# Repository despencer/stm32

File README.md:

# stm32
Some experimental and demo stuff for STM32 programming

# Building projects
mkdir build/<prjname>

cd buid/<prjname>

cmake <prjpath> -DBOARD=<board>

make

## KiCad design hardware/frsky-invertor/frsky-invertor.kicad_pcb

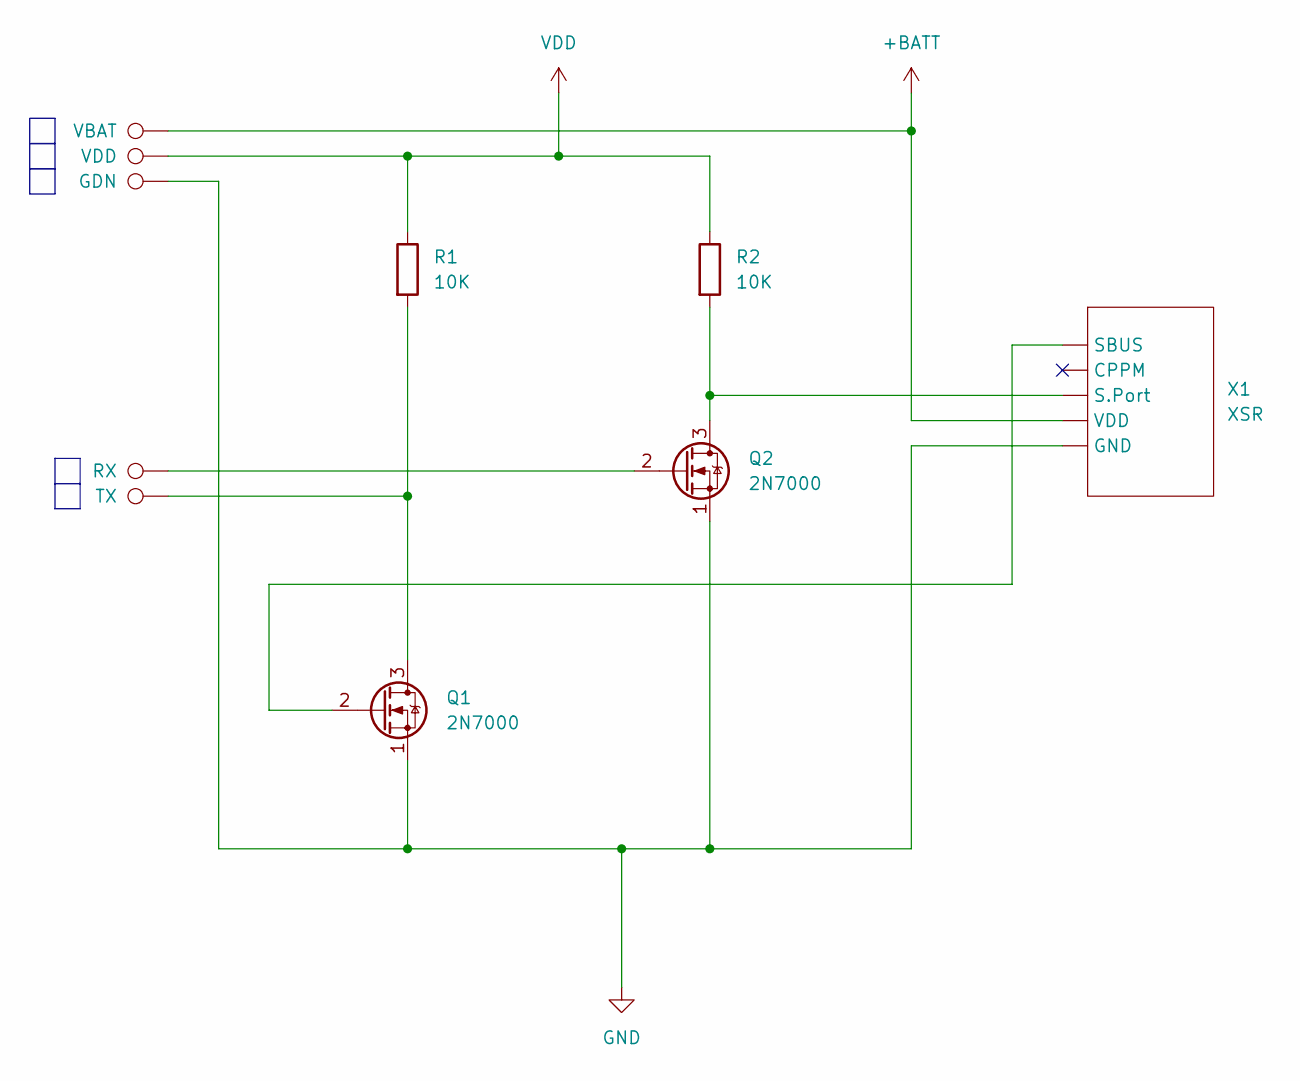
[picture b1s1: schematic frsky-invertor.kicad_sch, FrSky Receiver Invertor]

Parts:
Q1, Q2: 2N7000; TO-92_Inline_Wide
R1, R2: 10K; R_Axial_DIN0411_L9.9mm_D3.6mm_P12.70mm_Horizontal
TP1: GDN; SolderWire-0.1sqmm_1x01_D0.4mm_OD1mm
TP2: VDD; SolderWire-0.1sqmm_1x01_D0.4mm_OD1mm
TP3: VBAT; SolderWire-0.1sqmm_1x01_D0.4mm_OD1mm
TP4: TX; SolderWire-0.1sqmm_1x01_D0.4mm_OD1mm
TP5: RX; SolderWire-0.1sqmm_1x01_D0.4mm_OD1mm
X1: XSR

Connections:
+BATT: TP3.1, X1.4 (VDD)
GND: Q1.1 (S), Q2.1 (S), TP1.1, X1.5 (GND)
unnamed: Q1.3 (D), R1.2, TP4.1
unnamed: Q1.2 (G), X1.1 (SBUS)
unnamed: Q2.3 (D), R2.2, X1.3 (S.Port)
unnamed: Q2.2 (G), TP5.1
VDD: R1.1, R2.1, TP2.1

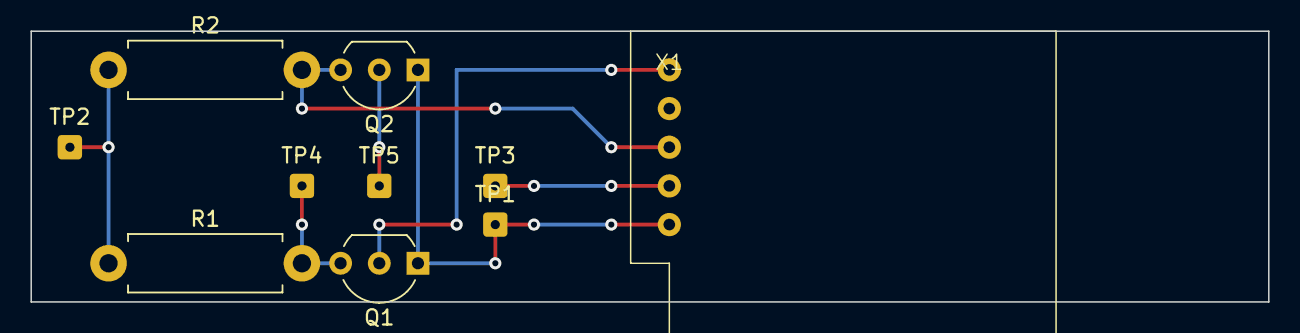
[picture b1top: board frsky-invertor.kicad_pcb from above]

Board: 2 copper layers, 81.3 x 17.8 mm, 10 parts (0 on the bottom side), 7 nets.

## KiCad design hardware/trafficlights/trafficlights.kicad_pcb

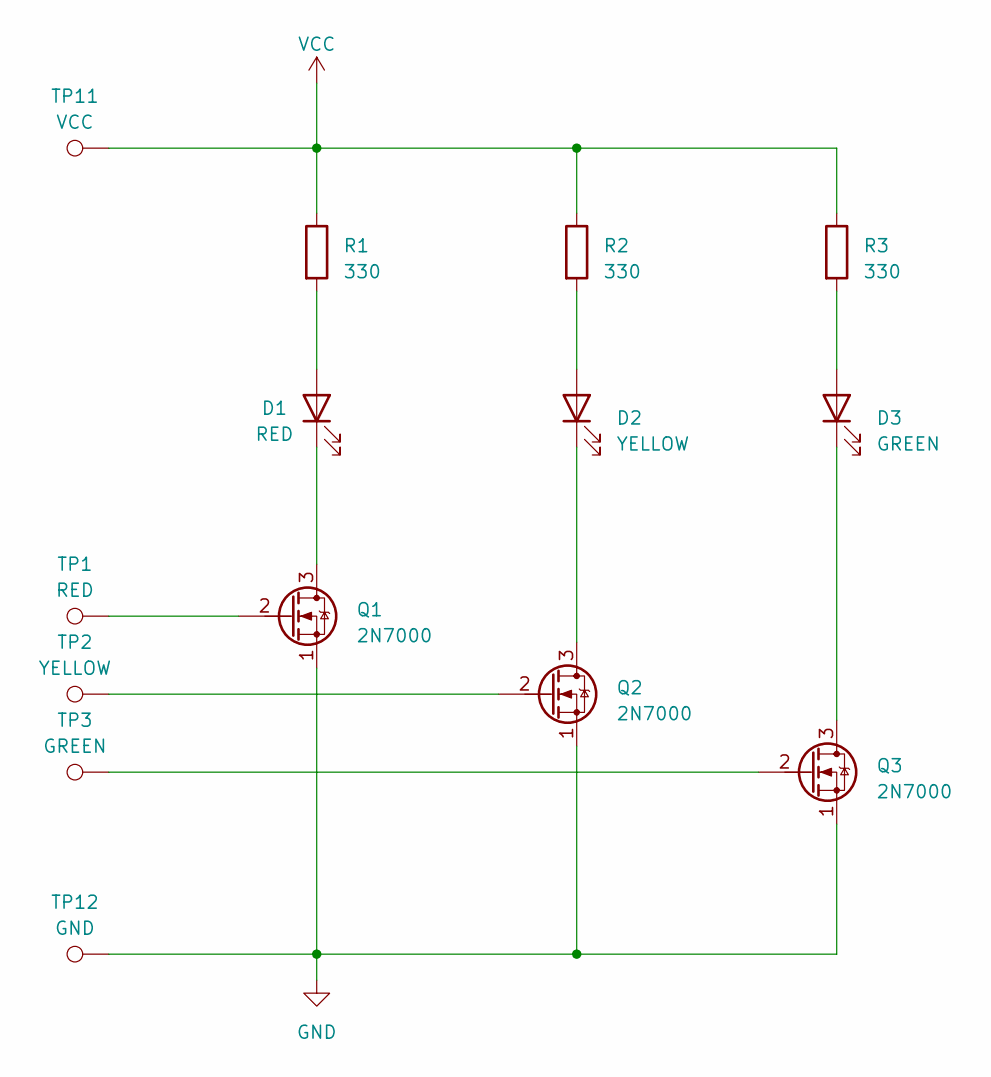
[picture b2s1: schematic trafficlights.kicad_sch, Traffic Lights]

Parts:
D1: RED; LED_D5.0mm
D2: YELLOW; LED_D5.0mm
D3: GREEN; LED_D5.0mm
Q1, Q2, Q3: 2N7000; TO-92_Inline_Wide
R1, R2, R3: 330; R_Axial_DIN0414_L11.9mm_D4.5mm_P15.24mm_Horizontal
TP1: RED; SolderWire-0.1sqmm_1x01_D0.4mm_OD1mm
TP2: YELLOW; SolderWire-0.1sqmm_1x01_D0.4mm_OD1mm
TP3: GREEN; SolderWire-0.1sqmm_1x01_D0.4mm_OD1mm
TP11: VCC; SolderWire-0.1sqmm_1x01_D0.4mm_OD1mm
TP12: GND; SolderWire-0.1sqmm_1x01_D0.4mm_OD1mm

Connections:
GND: Q1.1 (S), Q2.1 (S), Q3.1 (S), TP12.1
unnamed: D1.2 (A), R1.2
unnamed: D1.1 (K), Q1.3 (D)
unnamed: D2.2 (A), R2.2
unnamed: D2.1 (K), Q2.3 (D)
unnamed: D3.2 (A), R3.2
unnamed: D3.1 (K), Q3.3 (D)
unnamed: Q1.2 (G), TP1.1
unnamed: Q2.2 (G), TP2.1
unnamed: Q3.2 (G), TP3.1
VCC: R1.1, R2.1, R3.1, TP11.1

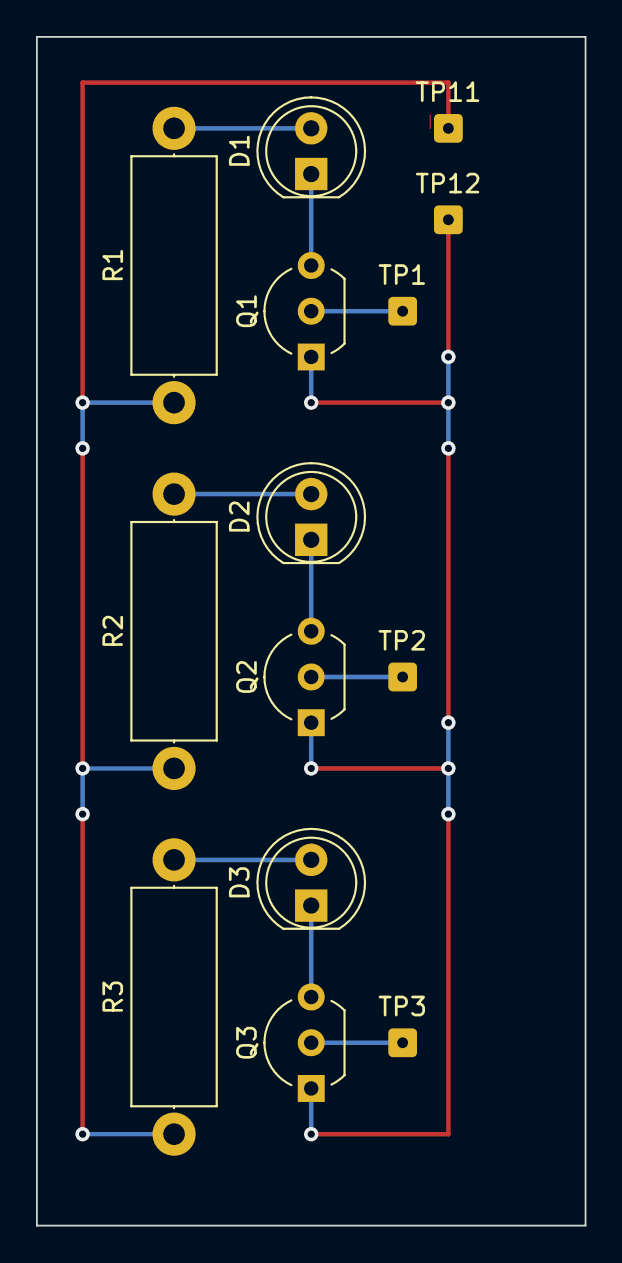
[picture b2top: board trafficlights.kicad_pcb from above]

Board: 2 copper layers, 30.5 x 66.0 mm, 14 parts (0 on the bottom side), 11 nets.

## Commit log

2022-12-26 Initial fill-in.
2022-12-26 First build.
2023-01-18 Remove build directories from tracking.
2023-01-18 CMake files were split into common and specific.
2023-01-19 Added board and cpu specifications.
2023-01-19 BlackPill added
2023-01-20 Split compiler options into general STM32, cpu-specific and libopencm3 specific.
2023-01-24 Made miniblink for BluePill and BlackPill
2023-01-30 Fastener for BlackPill created.
2023-02-23 Experiments with Black Pill board handlers.
2023-02-23 Initial setup for trafficlights demo
2023-02-24 CMake is ready and can build.
2023-03-16 FreeRTOS blinking proof of concept.
2023-03-23 CMake housekeeping and moving contents of FreeRTOSConfig to the general place.
2023-04-12 Another pin for on-off added.
2023-04-18 Setup schematics for traffic lights hardware module.
2023-05-09 Header for project definitions added.
2023-05-09 Made PCB design for perforated board.
2023-05-09 Transferred specific STM32F4 options into general stm32 cmake file
2023-05-09 Moved general linker options into stm32 cmake
2023-05-11 cmake finalization for libopencm3 and freertos.
2023-05-11 Created directory opencm3hal for board and cpu specifics.
2023-05-27 Board layout added.
2023-05-27 Moved linker file to cpu-specific folders
2023-05-27 Clock frequency selection moved to libopencm2 cmake file
2023-06-03 setup_clock was moved to HAL
2023-10-15 HAL files generator created.
2023-10-15 HAL generator for c files added.
2023-10-15 Integrated HAL generator into CMake.
2023-10-15 Made CMake to generate HAL files.
2023-10-15 Make target buildable.
2023-10-18 Traffic Light project builded.
2023-10-19 Strcture for port description implemented. Traffic lights is working.
2024-01-06 Adjusted for fresh linux installation.
2024-01-07 Moved examples into dedicated dir.
2024-01-08 Moved common definitions into lab.cmake.
2024-01-10 Configuration file for projects added.
2024-01-12 Config parsing functionality moved into config.py
2024-01-12 Added initial port HAL generation with proper dependency handling.
2024-01-16 Rewrite opencmp3 HAL using yaml configuration.
2024-01-16 Miniblink is working with the new HAL.
2024-01-16 Rewrited trafficlights demo with new HAL.
2024-01-18 Added initial code for serial transmission.
2024-01-18 Made client code (main.c)
2024-01-19 Empty build for usart.
2024-01-22 Processing of USART parameters added.
2024-01-23 USART port initialization added.
2024-01-23 UART example is ready for run.
2024-01-29 Example project echo is initiated.
2024-02-01 Serial echo project with queues is working.
2024-02-05 A little bugfix.
2024-02-05 Create empty schematic for FrSky invertor.
2024-02-12 Electrical schema created for FrSky invertor.
2024-02-12 Footprints added for resistors and connectors were changed to testpoints.
2024-02-13 PCB layout created.
2025-06-04 Heartbeat for command center was implemented.
2025-06-13 Channel type added as a parameter
2025-06-13 Heartbeat messages for BlackPill.
2025-06-13 Add serial communication to reader.
2025-06-15 Reset example initiated.
2025-06-15 Actual reset was added.
2025-06-17 Reset counter was added.
2025-06-18 Code for communicate with bootloader initiated.
2025-06-19 Bootloader GETID command added.
2025-06-19 Create firmware and cc for reset in bootloader mode.
2025-06-20 Fixed 8/9 bits USART problem and made Bootloader available after soft reset.
2025-06-22 Memory reader from MCU is initiated.
2025-07-01 Flash reader using STM32 factory bootloader implemented.
2025-11-24 A boilerplate code for flash writing.
2025-11-26 SLPX documentation.
2025-11-26 Documentation bugfix
2025-12-10 Heartbeat lab rewritten on a new SLPX protocol.
2025-12-10 Bugfixing done.
2025-12-18 Make SLPX working in Python/pipe mode.
2025-12-18 Made heartbeat working in SLPX mode in firmware.
2025-12-18 Queues for USART handling were switched to static allocation.
2025-12-18 A little renaming.
2025-12-22 Mutexes for SLPX introduced.
2025-12-23 SLPX listener added.
2025-12-23 Mutexe locks for SLPX transmits were added.
2025-12-25 Added calling of slpx_send from different tasks.
2025-12-25 SLPX receiver was added.
2025-12-25 Acknowlegment message was added.
2025-12-26 Refactor of comm CMAKE module.
2026-01-01 Parsers were added for SLPX_OPEN_ACK and SLPX_HEARTBEAT.
2026-01-01 SLPX reading was moved into a separated thread.
2026-01-02 Command interface for SLPX.
2026-01-02 Mutex was added for SLPX transmission.
2026-01-02 Command Manager was added for cc.
2026-01-06 SLPX_RESET command handler was added.
2026-01-09 Message SLPX_CLOSE sending was added for system shutdown.
2026-01-23 SLPX Start/Shutdown workflow was reworked. Entering bootload mode was added.
2026-02-10 Bootload mode entering was reworked, commands are now confirmed.
2026-02-12 Memory reading from STM32 bootloader via USART was added.
2026-02-19 Common bootloader code was transfered to a dedicated file.
2026-02-25 Writing code to STM32 was added.
2026-03-16 Jumping back to the application code from bootloader was added for memory reading.
2026-03-16 Added switch for manual enter to a bootloader mode (by pressing physical button).
2026-03-16 Returning to an appmode and starting in a bootloader mode was added to memory writer.
